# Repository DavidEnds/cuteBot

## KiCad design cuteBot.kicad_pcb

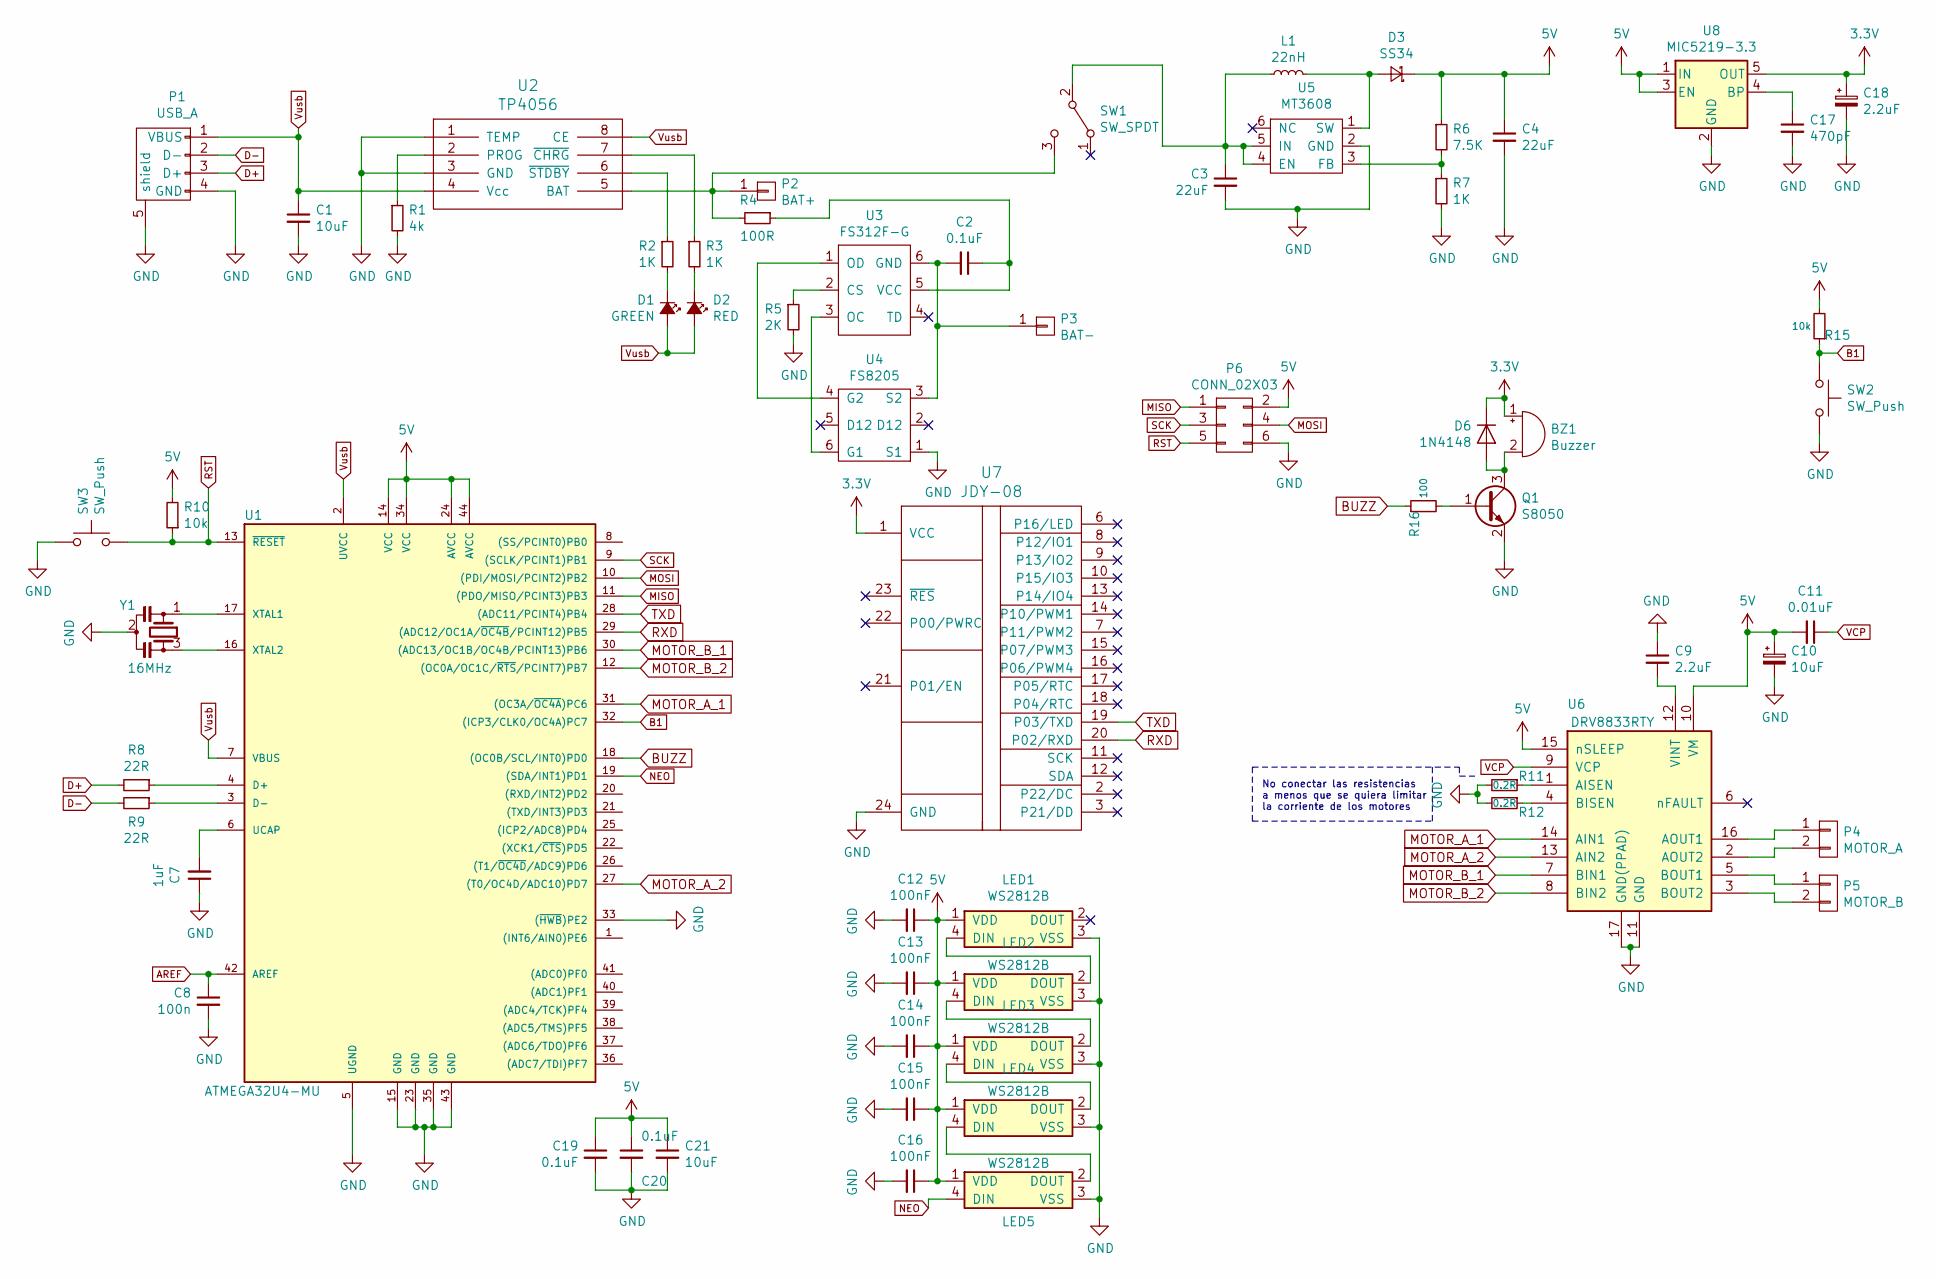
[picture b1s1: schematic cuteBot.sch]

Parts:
BZ1: Buzzer; Buzzer-7.5x7.5mm
C1, C10, C21: 10uF; C_0603
C2, C19, C20: 0.1uF; C_0603
C3, C4: 22uF; C_1812
C7: 1uF; C_0603
C8: 100n; C_0603
C9, C18: 2.2uF; C_0603
C11: 0.01uF; C_0603
C12, C13, C14, C15, C16: 100nF; C_0603
C17: 470pF; C_0603
D1: GREEN; LED_0603
D2: RED; LED_0603
D3: SS34; D_SMA
D6: 1N4148; D_MicroMELF
L1: 22nH; L_7.3x7.3_H4.5
LED1, LED2, LED3, LED4, LED5: WS2812B; LED_SK6812MINI_PLCC4_3.5x3.5mm_P1.75mm
P1: USB_A; USB_Micro-B_Molex-105017-0001
P2: BAT+; Test_Point_Pad_d1.0mm
P3: BAT-; Test_Point_Pad_d1.0mm
P4: MOTOR_A; SMD_2pin_Solderpad
P5: MOTOR_B; SMD_2pin_Solderpad
P6: CONN_02X03; 2X3_SMT_POSTS
Q1: S8050; SOT-23
R1: 4k; R_0603
R2, R3, R7: 1K; R_0603
R4: 100R; R_0603
R5: 2K; R_0603
R6: 7.5K; R_0603
R8, R9: 22R; R_0603
R10, R15: 10k; R_0603
R11, R12: 0.2R; R_0603
R16: 100; R_0603
SW1: SW_SPDT; SW_SPDT_PCM12
SW2, SW3: SW_Push; SW_SPST_B3U-3000P
U1: ATMEGA32U4-MU; QFN-44-1EP_7x7mm_Pitch0.5mm
U2: TP4056; HTSOP-8-1EP_3.9x4.9mm_Pitch1.27mm_ThermalVias
U3: FS312F-G; SOT-23-6
U4: FS8205; SOT-23-6
U5: MT3608; SOT-23-6
U6: DRV8833RTY; WQFN-16-1EP_4x4mm_Pitch0.65mm
U7: JDY-08
U8: MIC5219-3.3; SOT-23-5
Y1: 16MHz; RESONATOR-SMD-3.2X1.3

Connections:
3.3V: BZ1.1 (-), C18.1, D6.1 (K), U7.1 (VCC), U8.5 (OUT)
5V: C4.1, C10.1, C11.2, C12.1, C13.1, C14.1, C15.1, C16.1, C19.1, C20.1, C21.1, D3.1 (K), LED1.1 (VDD), LED2.1 (VDD), LED3.1 (VDD), LED4.1 (VDD), LED5.1 (VDD), P6.2, R6.1, R10.2, R15.2, U1.14 (VCC), U1.24 (AVCC), U1.34 (VCC), U1.44 (AVCC), U6.10 (VM), U6.15 (nSLEEP), U8.1 (IN), U8.3 (EN)
AREF: C8.1, U1.42 (AREF)
B1: R15.1, SW2.1, U1.32 ((ICP3/CLK0/OC4A)PC7)
BUZZ: R16.1, U1.18 ((OC0B/SCL/INT0)PD0)
D+: P1.3 (D+), R8.2
D-: P1.2 (D-), R9.2
GND: C1.2, C3.2, C4.2, C7.1, C8.2, C9.1, C10.2, C12.2, C13.2, C14.2, C15.2, C16.2, C17.2, C18.2, C19.2, C20.2, C21.2, LED1.3 (VSS), LED2.3 (VSS), LED3.3 (VSS), LED4.3 (VSS), LED5.3 (VSS), P1.4 (GND), P1.5 (shield), P6.6, Q1.2 (E), R1.2, R5.2, R7.2, R11.2, R12.2, SW2.2, SW3.1, U1.5 (UGND), U1.15 (GND), U1.23 (GND), U1.33 ((~HWB~)PE2), U1.35 (GND), U1.43 (GND), U2.1 (TEMP), U2.3 (GND), U4.1 (S1), U5.2 (GND), U6.11 (GND), U6.17 (GND(PPAD)), U7.24 (GND), U8.2 (GND), Y1.2
MISO: P6.1, U1.11 ((PDO/MISO/PCINT3)PB3)
MOSI: P6.4, U1.10 ((PDI/MOSI/PCINT2)PB2)
MOTOR_A_1: U1.31 ((OC3A/~OC4A~)PC6), U6.14 (AIN1)
MOTOR_A_2: U1.27 ((T0/OC4D/ADC10)PD7), U6.13 (AIN2)
MOTOR_B_1: U1.30 ((ADC13/OC1B/OC4B/PCINT13)PB6), U6.7 (BIN1)
MOTOR_B_2: U1.12 ((OC0A/OC1C/~RTS~/PCINT7)PB7), U6.8 (BIN2)
NEO: LED5.4 (DIN), U1.19 ((SDA/INT1)PD1)
unnamed: BZ1.2 (+), D6.2 (A), Q1.3 (C)
unnamed: C2.1, R4.1, U3.5 (VCC)
unnamed: C2.2, P3.1, U3.6 (GND), U4.3 (S2)
unnamed: C3.1, L1.1, SW1.2 (B), U5.4 (EN), U5.5 (IN)
unnamed: C7.2, U1.6 (UCAP)
unnamed: C9.2, U6.12 (VINT)
unnamed: C17.1, U8.4 (BP)
unnamed: D1.1 (K), R2.2
unnamed: D2.1 (K), R3.2
unnamed: D3.2 (A), L1.2, U5.1 (SW)
unnamed: LED1.4 (DIN), LED2.2 (DOUT)
unnamed: LED2.4 (DIN), LED3.2 (DOUT)
unnamed: LED3.4 (DIN), LED4.2 (DOUT)
unnamed: LED4.4 (DIN), LED5.2 (DOUT)
unnamed: P2.1, R4.2, SW1.3 (C), U2.5 (BAT)
unnamed: P4.1, U6.16 (AOUT1)
unnamed: P4.2, U6.2 (AOUT2)
unnamed: P5.1, U6.5 (BOUT1)
unnamed: P5.2, U6.3 (BOUT2)
unnamed: Q1.1 (B), R16.2
unnamed: R1.1, U2.2 (PROG)
unnamed: R2.1, U2.6 (~STDBY)
unnamed: R3.1, U2.7 (~CHRG)
unnamed: R5.1, U3.2 (CS)
unnamed: R6.2, R7.1, U5.3 (FB)
unnamed: R8.1, U1.4 (D+)
unnamed: R9.1, U1.3 (D-)
unnamed: R11.1, U6.1 (AISEN)
unnamed: R12.1, U6.4 (BISEN)
unnamed: U1.16 (XTAL2), Y1.3
unnamed: U1.17 (XTAL1), Y1.1
unnamed: U3.1 (OD), U4.4 (G2)
unnamed: U3.3 (OC), U4.6 (G1)
RST: P6.5, R10.1, SW3.2, U1.13 (~RESET~)
RXD: U1.29 ((ADC12/OC1A/~OC4B~/PCINT12)PB5), U7.20 (P02/RXD)
SCK: P6.3, U1.9 ((SCLK/PCINT1)PB1)
TXD: U1.28 ((ADC11/PCINT4)PB4), U7.19 (P03/TXD)
VCP: C11.1, U6.9 (VCP)
Vusb: C1.1, D1.2 (A), D2.2 (A), P1.1 (VBUS), U1.2 (UVCC), U1.7 (VBUS), U2.4 (Vcc), U2.8 (CE)

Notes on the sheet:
No conectar las resistencias a menos que se quiera limitar la corriente de los motores

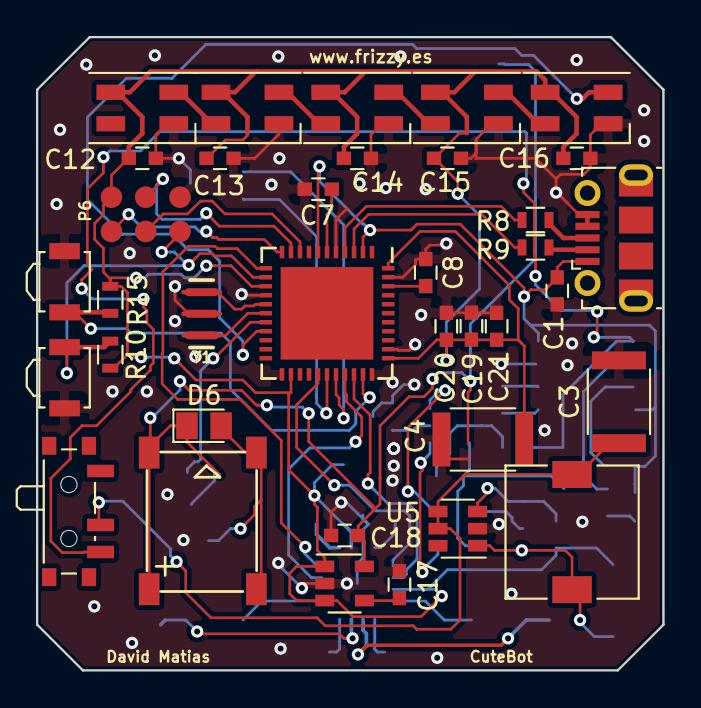
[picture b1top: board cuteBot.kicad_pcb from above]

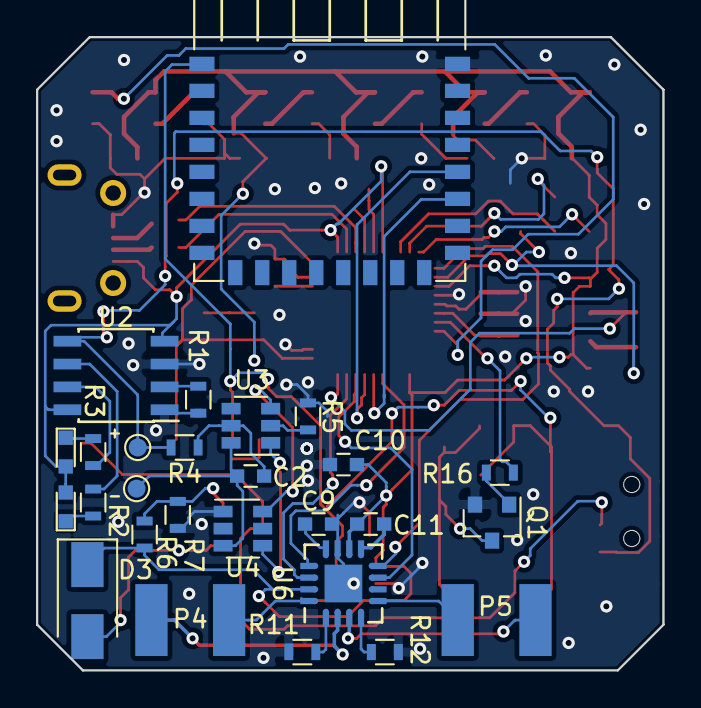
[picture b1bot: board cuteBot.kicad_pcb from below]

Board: 2 copper layers, 34.8 x 35.2 mm, 63 parts (27 on the bottom side), 54 nets.

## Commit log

2018-12-16 Esquema comenzado y simbolos propios creados
2019-01-02 Añadidos algunos componentes principales
    Añadidos los leds. puente en H y pulsador.
2019-02-11 Añadiendo los componentes, hay algunos errores de footprint
2019-02-11 Footprints correctos
2019-02-11 Error en el S8050 subsanado
2019-02-11 Colocando los componentes
2019-02-17 Enrutando
2019-02-17 Resonador cambiado
2019-02-17 Leds RX/TX eliminados
2019-02-17 Enrutado avanzando. 65 nets
2019-02-18 26 nets restantes
2019-02-18 Enrutado comleto
2019-02-18 Colocando serigrafias
2019-02-18 Serigrafía terminada
2019-03-10 Errores corregidos.
    Vias que provocaban un corto, pinout del Q1 erróneo y flag de los neopixel no conectado al micro.
